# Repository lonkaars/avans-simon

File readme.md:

# avans-simon

(In Dutch)

cool project

deze keer doe ik 'm alleen, dus alles staat nu hier (met documentatie enzo)

## todo

- [x] software
- [x] hardware (+schema's)
- [x] software ontwerp (activiteitsdiagram)
- [x] blokschema, functiebeschrijving, en spelverloop
- [x] urenrapportage

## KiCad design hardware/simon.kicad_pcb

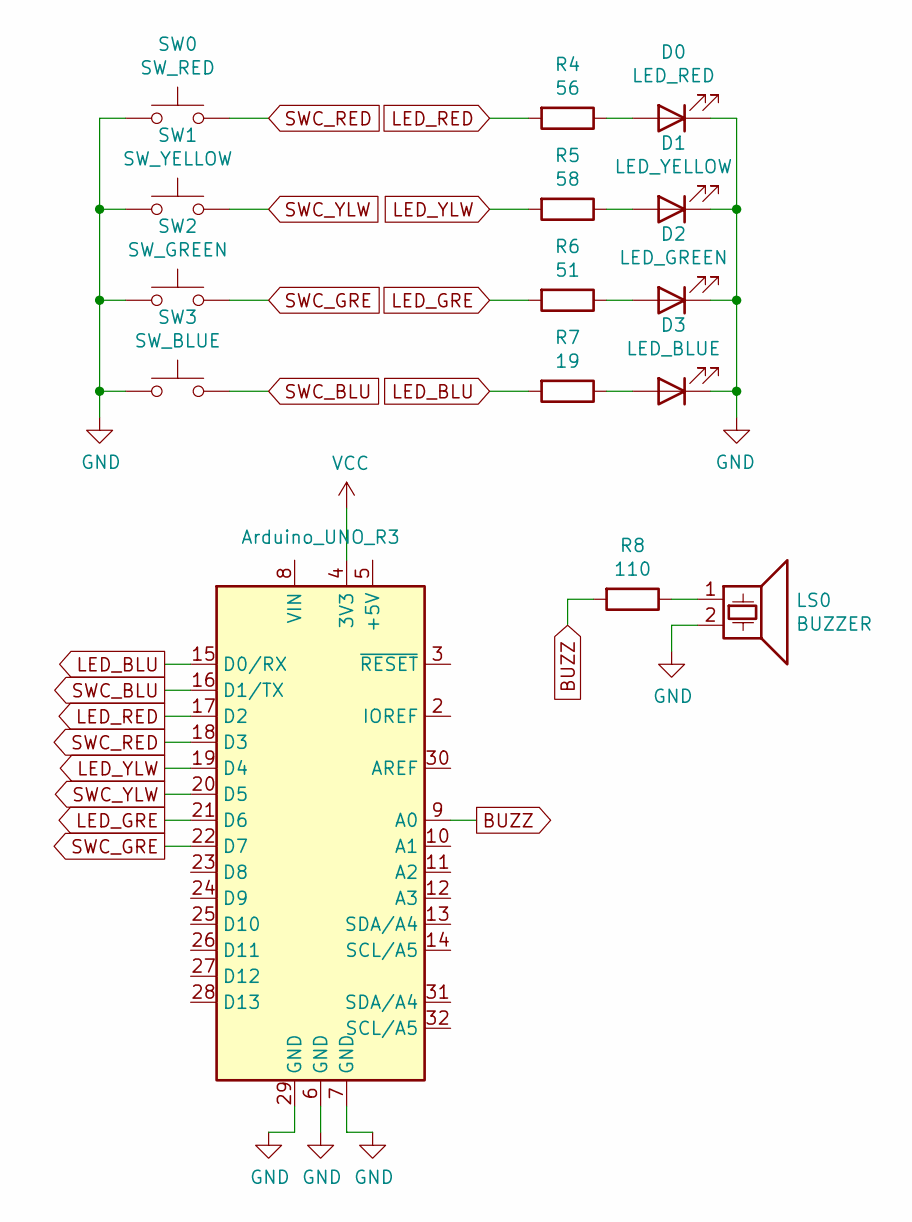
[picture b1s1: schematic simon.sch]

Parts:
A0: Arduino_UNO_R3
D0: LED_RED; LED_D3.0mm
D1: LED_YELLOW; LED_D3.0mm
D2: LED_GREEN; LED_D3.0mm
D3: LED_BLUE; LED_D3.0mm
LS0: BUZZER; Buzzer_12x9.5RM7.6
R4: 56; R_Axial_DIN0207_L6.3mm_D2.5mm_P10.16mm_Horizontal
R5: 58; R_Axial_DIN0207_L6.3mm_D2.5mm_P10.16mm_Horizontal
R6: 51; R_Axial_DIN0207_L6.3mm_D2.5mm_P10.16mm_Horizontal
R7: 19; R_Axial_DIN0207_L6.3mm_D2.5mm_P10.16mm_Horizontal
R8: 110; R_Axial_DIN0207_L6.3mm_D2.5mm_P10.16mm_Horizontal
SW0: SW_RED; SW_PUSH_6mm_H4.3mm
SW1: SW_YELLOW; SW_PUSH_6mm_H4.3mm
SW2: SW_GREEN; SW_PUSH_6mm_H4.3mm
SW3: SW_BLUE; SW_PUSH_6mm_H4.3mm

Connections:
BUZZ: A0.9 (A0), R8.2
GND: A0.6 (GND), A0.7 (GND), A0.29 (GND), D0.1 (K), D1.1 (K), D2.1 (K), D3.1 (K), LS0.2, SW0.1, SW1.1, SW2.1, SW3.1
LED_BLU: A0.15 (D0/RX), R7.2
LED_GRE: A0.21 (D6), R6.2
LED_RED: A0.17 (D2), R4.2
LED_YLW: A0.19 (D4), R5.2
unnamed: D0.2 (A), R4.1
unnamed: D1.2 (A), R5.1
unnamed: D2.2 (A), R6.1
unnamed: D3.2 (A), R7.1
unnamed: LS0.1, R8.1
SWC_BLU: A0.16 (D1/TX), SW3.2
SWC_GRE: A0.22 (D7), SW2.2
SWC_RED: A0.18 (D3), SW0.2
SWC_YLW: A0.20 (D5), SW1.2
VCC: A0.4 (3V3)

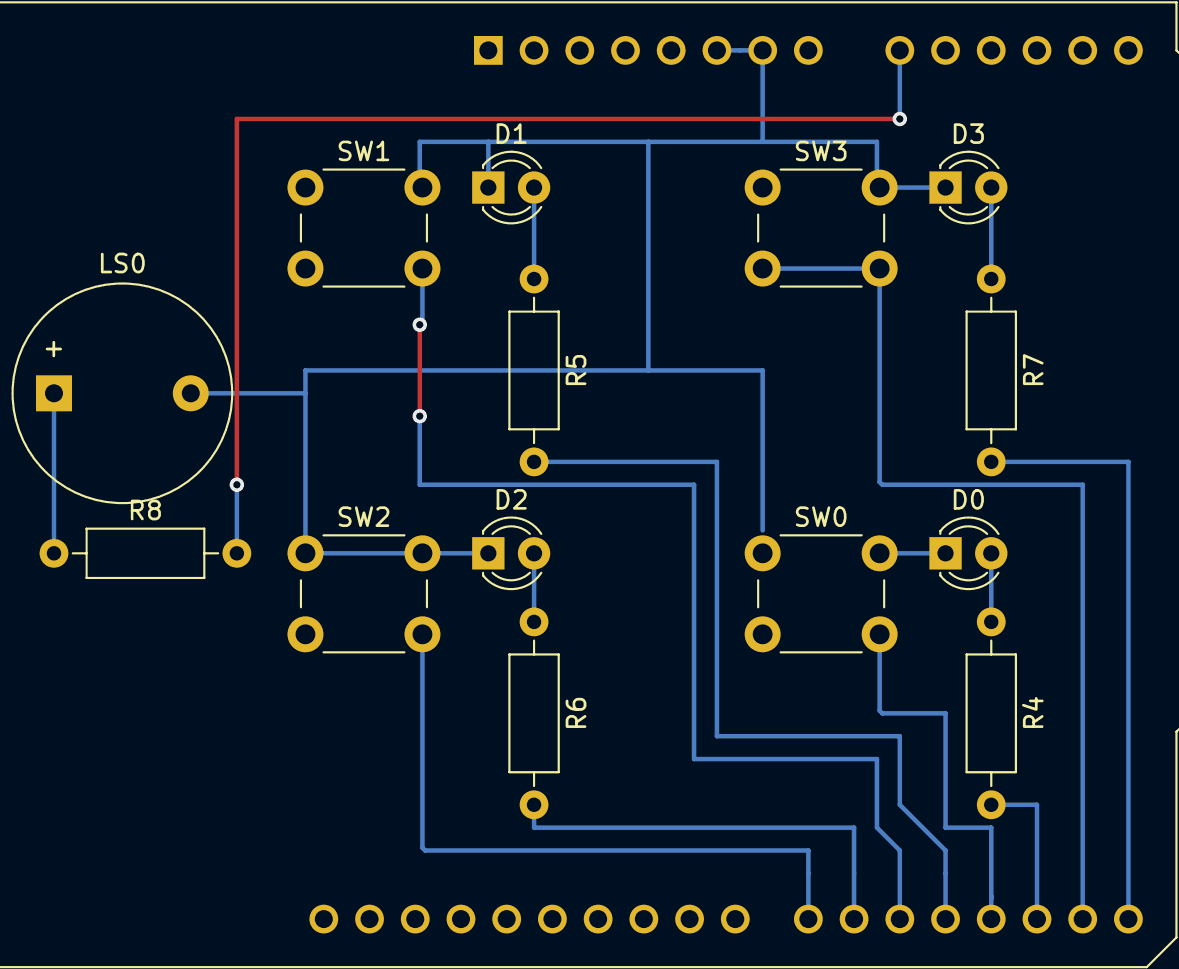
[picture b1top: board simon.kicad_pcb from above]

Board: 2 copper layers, 15 parts (0 on the bottom side), 15 nets.

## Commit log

2021-11-01 added gitignore and schematics beginnings
2021-11-01 metingen
2021-11-02 updated resistor values in hardware schematics
2021-11-02 hardware schematics done, test code included
2021-11-02 half baked code
2021-11-03 game werks
2021-11-03 added some comments
2021-11-04 software design done
2021-11-04 block diagram, fuction definitions and gameplay
2021-11-04 project done
2021-11-04 added schematics to design document
